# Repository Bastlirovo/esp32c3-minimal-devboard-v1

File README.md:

# esp32c3-minimal-devboard-v1
 Minimal devboard for ESP32-C3F module

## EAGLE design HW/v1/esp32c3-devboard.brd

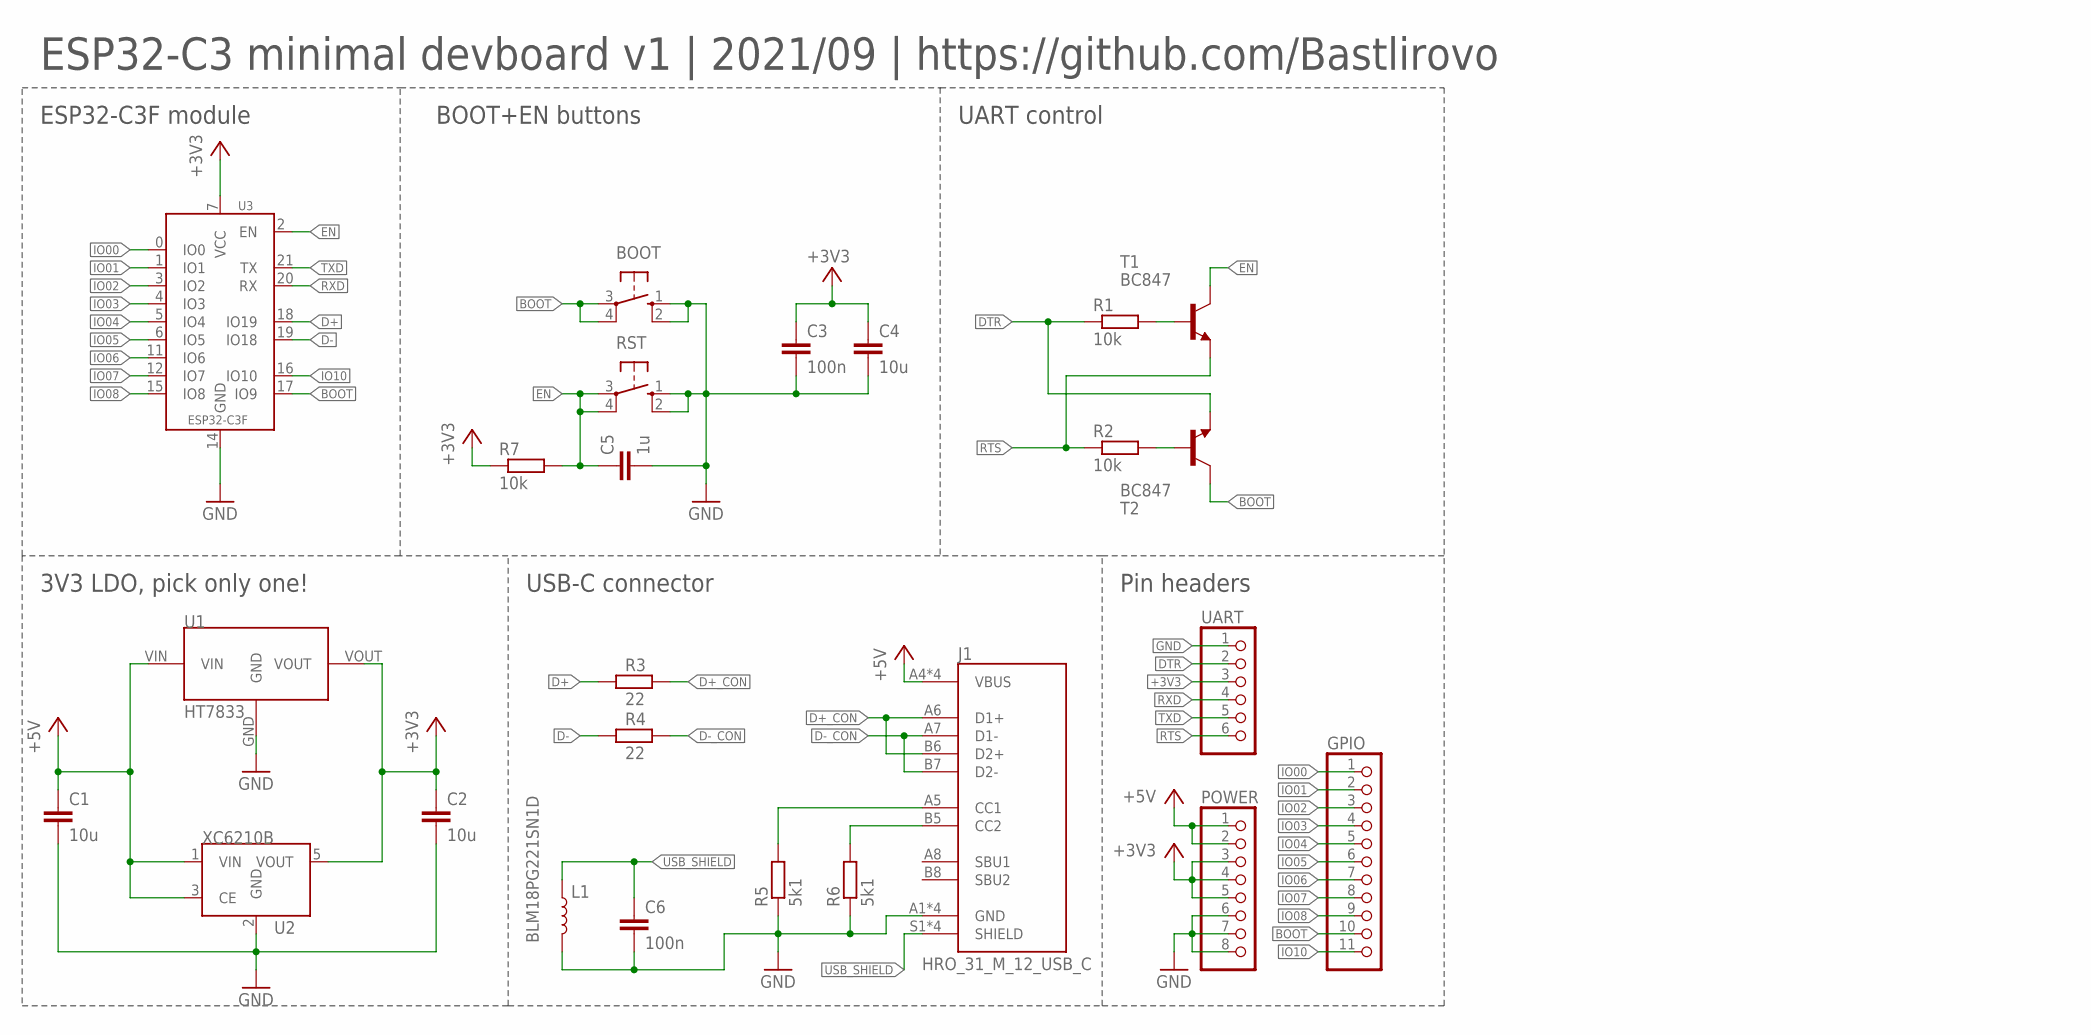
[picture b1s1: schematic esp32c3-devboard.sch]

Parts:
BOOT: 10-XX; B3F-10XX
C1, C2, C4: 10u; C0603
C3, C6: 100n; C0603
C5: 1u; C0603
GPIO: PINHD-1X11; 1X11
J1: HRO_31_M_12_USB_C
L1: BLM18PG221SN1D; 0603
POWER: PINHD-1X8; 1X08
R1, R2, R7: 10k; R0603
R3, R4: 22; R0603
R5, R6: 5k1; R0603
RST: 10-XX; B3F-10XX
T1, T2: BC847; SOT23
U1: HT7833; SOT89
U2: XC6210; SOT-23-5
U3: ESP32-C3F
UART: PINHD-1X6; 1X06

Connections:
+3V3: C2.1, C3.1, C4.1, POWER.3, POWER.4, POWER.5, R7.1, U1.VOUT, U2.5 (VOUT), U3.7 (VCC), UART.3
+5V: C1.1, J1.A4 (VBUS), J1.A9 (VBUS), J1.B4 (VBUS), J1.B9 (VBUS), POWER.1, POWER.2, U1.VIN, U2.1 (VIN), U2.3 (CE)
BOOT: BOOT.3, BOOT.4 (P1), GPIO.10, T2.3 (C), U3.17 (IO9)
D+: R3.1, U3.18 (IO19)
D+_CON: J1.A6 (D1+), J1.B6 (D2+), R3.2
D-: R4.1, U3.19 (IO18)
D-_CON: J1.A7 (D1-), J1.B7 (D2-), R4.2
DTR: R1.1, T2.2 (E), UART.2
EN: C5.1, R7.2, RST.3, RST.4 (P1), T1.3 (C), U3.2 (EN)
GND: BOOT.1 (S), BOOT.2 (S1), C1.2, C2.2, C3.2, C4.2, C5.2, C6.2, J1.A1 (GND), J1.A12 (GND), J1.B1 (GND), J1.B12 (GND), L1.2, POWER.6, POWER.7, POWER.8, R5.1, R6.1, RST.1 (S), RST.2 (S1), U1.GND, U2.2 (GND), U3.14 (GND), UART.1
IO00: GPIO.1, U3.0 (IO0)
IO01: GPIO.2, U3.1 (IO1)
IO02: GPIO.3, U3.3 (IO2)
IO03: GPIO.4, U3.4 (IO3)
IO04: GPIO.5, U3.5 (IO4)
IO05: GPIO.6, U3.6 (IO5)
IO06: GPIO.7, U3.11 (IO6)
IO07: GPIO.8, U3.12 (IO7)
IO08: GPIO.9, U3.15 (IO8)
IO10: GPIO.11, U3.16 (IO10)
unnamed: R2.2, T2.1 (B)
unnamed: R1.2, T1.1 (B)
unnamed: J1.A5 (CC1), R5.2
unnamed: J1.B5 (CC2), R6.2
RTS: R2.1, T1.2 (E), UART.6
RXD: U3.20 (RX), UART.4
TXD: U3.21 (TX), UART.5
USB_SHIELD: C6.1, J1.S1 (SHIELD), J1.S2 (SHIELD), J1.S3 (SHIELD), J1.S4 (SHIELD), L1.1

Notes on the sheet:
ESP32-C3F module
BOOT+EN buttons
UART control
3V3 LDO, pick only one!
USB-C connector
Pin headers
ESP32-C3 minimal devboard v1 | 2021/09 | https://github.com/Bastlirovo

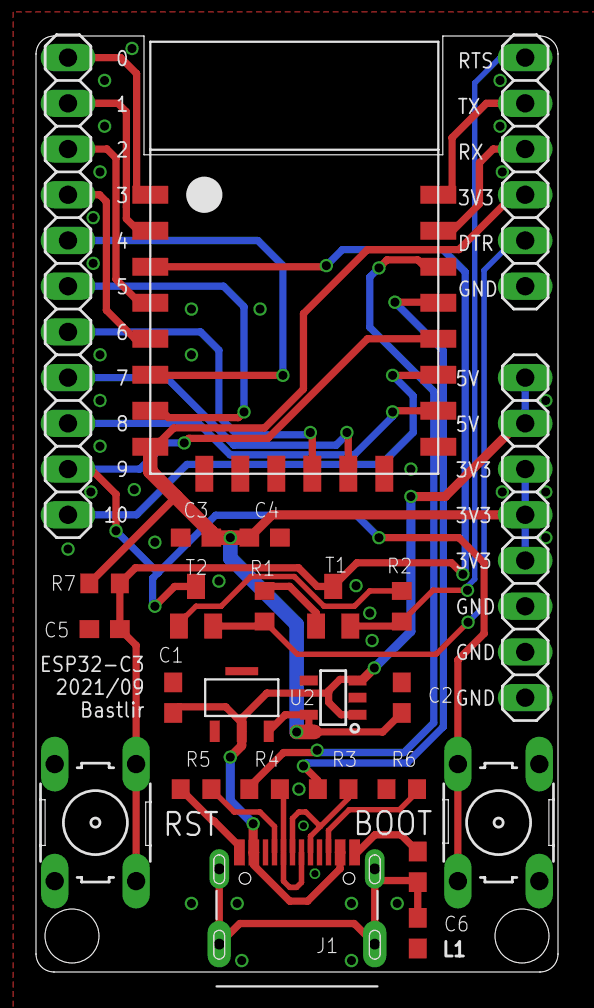
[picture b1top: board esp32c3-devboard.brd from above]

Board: 2 copper layers, 29.0 x 52.0 mm, 25 parts (0 on the bottom side), 28 nets.

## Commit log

2021-10-13 Initial commit of HW v1
2021-10-13 Added BOM with links

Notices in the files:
parts and their libraries:
SparkFun-Coils: Licensing: Creative Commons ShareAlike 4.0 International - https://creativecommons.org/licenses/by-sa/4.0
